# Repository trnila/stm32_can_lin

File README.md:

# STM32 Triple CAN/LIN USB bridge
STM32G4xx firmware written in Rust using the Embassy framework that bridges CAN-FD buses to Linux via USB using the `gs_usb` driver and socketCAN interface.

- 3x CAN-FD channels
    - configurable 120Ω termination resistor

## Build & flash & run
Install Rust via [rustup.rs](https://rustup.rs/).

Set `nSWBOOT0` to 0 using STM32CubeProgrammer for the first time, then connect the debugger and flash the device:
```sh
$ cargo run --release
```

Three socketCAN interfaces will appear, for example as `can0`, `can1`, and `can2`.
You can configure them using `ip` command:
```sh
$ sudo ip link set can0 type can bitrate 500000
$ sudo ip link set can0 up
```

After that, you can start sending and receiving CAN frames:
```sh
$ candump can0
$ cansend can0 123#abcd
```

## Configuration
All configurations must be done while the interface is in the `down` state.
```sh
$ sudo ip link set can0 down
```
After the configuration, bring the interface `up`.

### CAN-FD mode and data bitrate
Set CAN to 500 Kbps and CAN-FD to 1 Mbps:
```sh
$ sudo ip link set can0 type can bitrate 500000 fd on dbitrate 1000000
```

### 120Ω termination resistor
Termination resistor can be enabled in configuration mode via:
```sh
$ sudo ip link set can0 down
$ sudo ip link set can0 type can bitrate 500000 termination 120
$ sudo ip link set can0 up
```

### Persistent interface names
Configure udev rules (`/etc/udev/rules.d/91-scan.rules`) for persistent interface names:
```
SUBSYSTEM=="net", ENV{ID_SERIAL}=="trnila_STM32_CAN_LIN_1", ATTR{dev_id}=="0x0", NAME="scan0"
SUBSYSTEM=="net", ENV{ID_SERIAL}=="trnila_STM32_CAN_LIN_1", ATTR{dev_id}=="0x1", NAME="scan1"
SUBSYSTEM=="net", ENV{ID_SERIAL}=="trnila_STM32_CAN_LIN_1", ATTR{dev_id}=="0x2", NAME="scan2"
```
and then reload `sudo udevadm control --reload-rules` and re-plug the device.

## Test
Install following dependencies:
- uv
- [can-utils](https://github.com/linux-can/can-utils)

Next, connect the DUT's `can0` interface to the tester's `can1_0` interface, and so on. Then run:
```sh
$ CAN_IFACES=0:can0:can1_0,1:can1:can1_1,2:can2:can0_0 ./hw_test.py
```

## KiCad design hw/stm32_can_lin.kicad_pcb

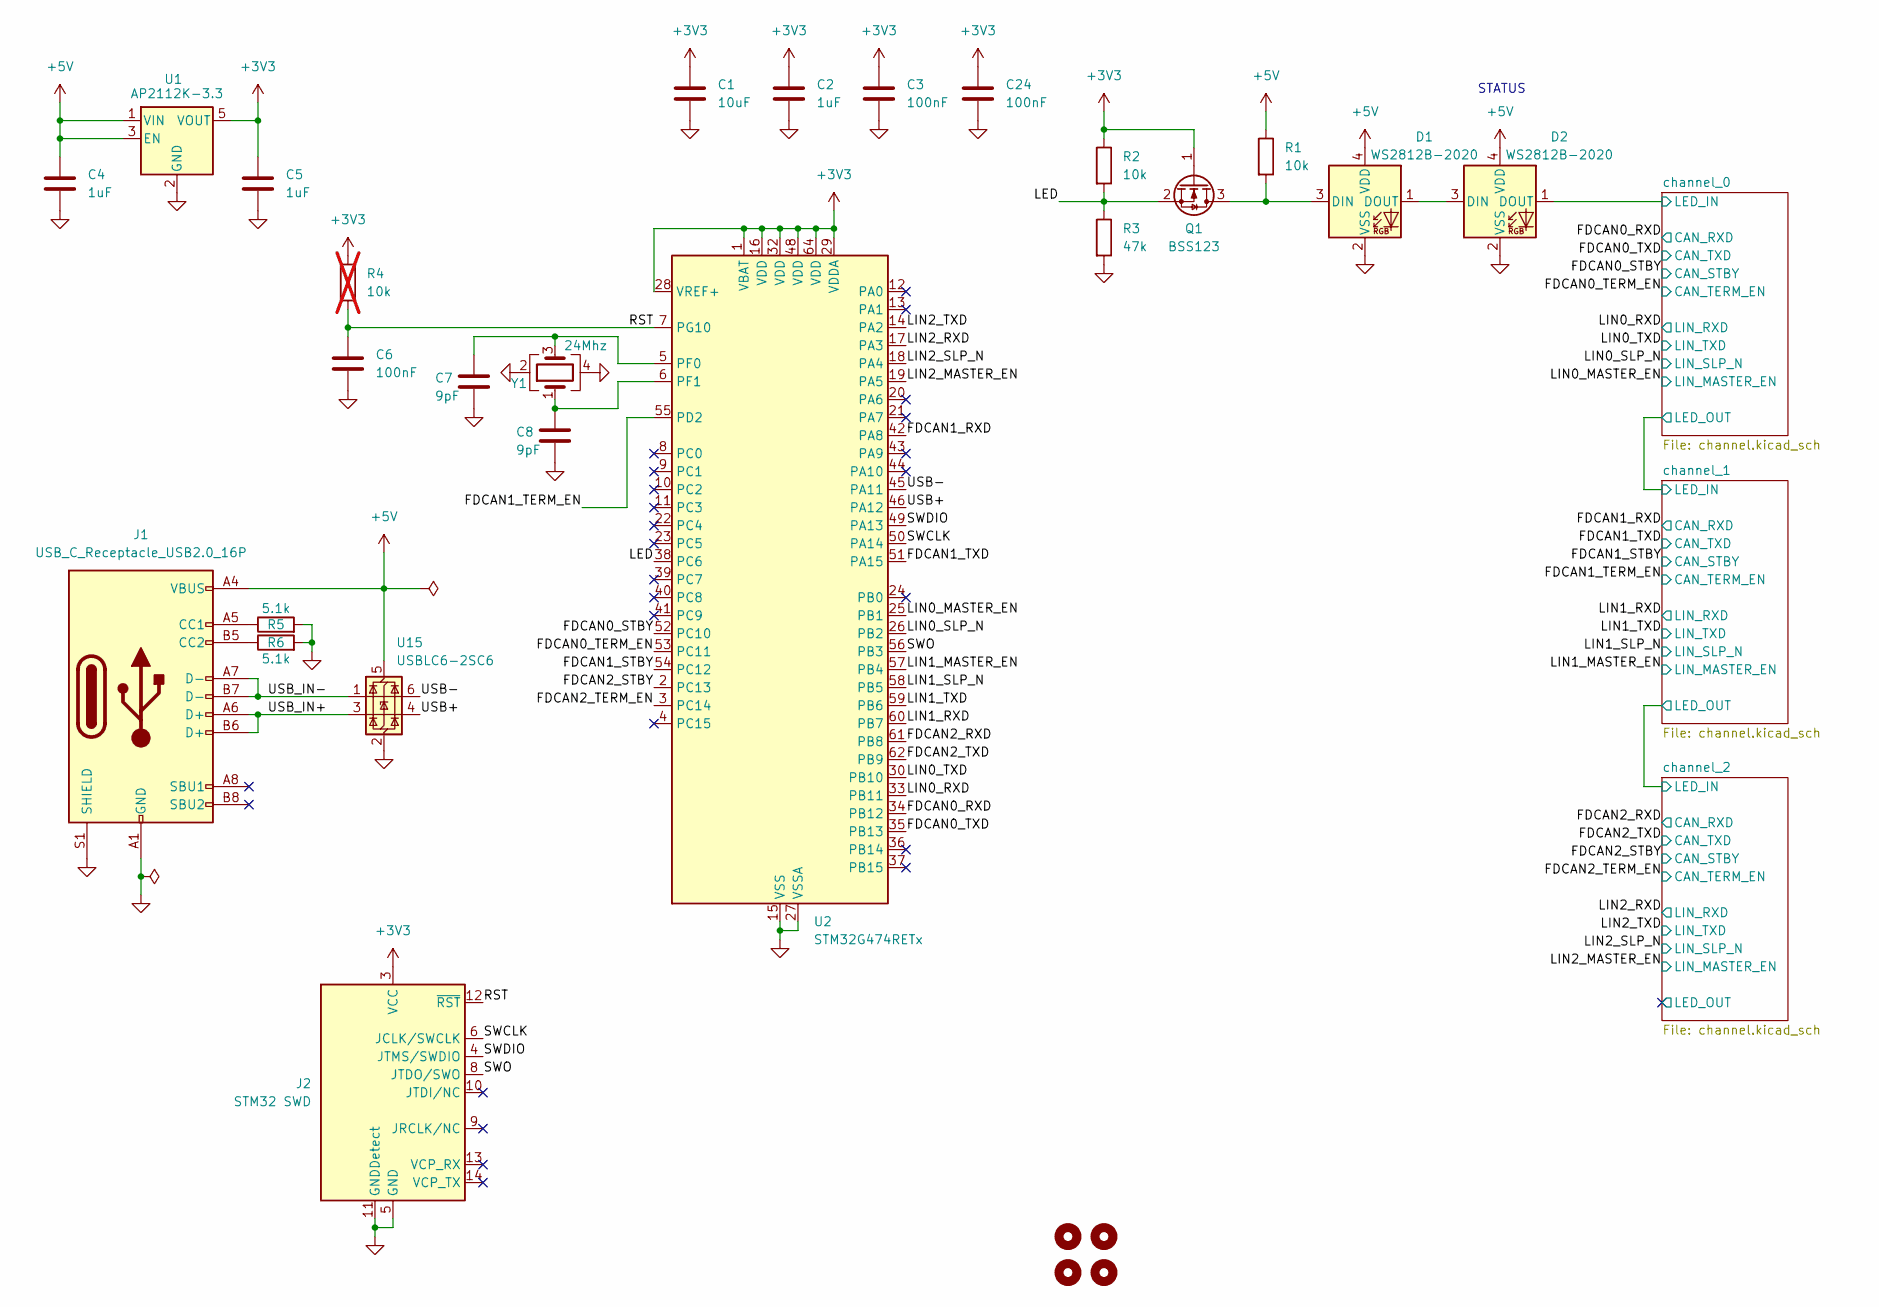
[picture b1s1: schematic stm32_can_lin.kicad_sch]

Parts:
C1: 10uF; C_0805_2012Metric_Pad1.18x1.45mm_HandSolder
C2, C4, C5: 1uF; C_0805_2012Metric_Pad1.18x1.45mm_HandSolder
C3, C6, C24: 100nF; C_0805_2012Metric_Pad1.18x1.45mm_HandSolder
C7, C8: 9pF; C_0805_2012Metric_Pad1.18x1.45mm_HandSolder
D1, D2: WS2812B-2020; LED_WS2812B-2020_PLCC4_2.0x2.0mm
H1, H2, H3, H4: MountingHole; MountingHole_3.2mm_M3
J1: USB_C_Receptacle_USB2.0_16P; USB_C_Receptacle_GCT_USB4105-xx-A_16P_TopMnt_Horizontal
J2: STM32 SWD; PinHeader_2x07_P1.27mm_Vertical_SMD
Q1: BSS123; SOT-23
R1, R2: 10k; R_0805_2012Metric_Pad1.20x1.40mm_HandSolder
R3: 47k; R_0805_2012Metric_Pad1.20x1.40mm_HandSolder
R4: 10k; R_0805_2012Metric_Pad1.20x1.40mm_HandSolder; not fitted
R5, R6: 5.1k; R_0805_2012Metric_Pad1.20x1.40mm_HandSolder
U1: AP2112K-3.3; SOT-23-5
U2: STM32G474RETx; LQFP-64_10x10mm_P0.5mm
U15: USBLC6-2SC6; SOT-23-6
Y1: 24Mhz; Crystal_SMD_3225-4Pin_3.2x2.5mm_HandSoldering

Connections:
+3V3: C1.1, C2.1, C3.1, C5.1, C24.1, J2.3 (VCC), Q1.1 (G), R2.1, R4.1, U1.5 (VOUT), U2.1 (VBAT), U2.16 (VDD), U2.28 (VREF+), U2.29 (VDDA), U2.32 (VDD), U2.48 (VDD), U2.64 (VDD); also elsewhere on the board
+5V: C4.1, D1.4 (VDD), D2.4 (VDD), J1.A4 (VBUS), J1.A9 (VBUS), J1.B4 (VBUS), J1.B9 (VBUS), R1.1, U1.1 (VIN), U1.3 (EN), U15.5 (VBUS); also elsewhere on the board
/FDCAN0_RXD: U2.34 (PB12); also elsewhere on the board
/FDCAN0_STBY: U2.52 (PC10); also elsewhere on the board
/FDCAN0_TERM_EN: U2.53 (PC11); also elsewhere on the board
/FDCAN0_TXD: U2.35 (PB13); also elsewhere on the board
/FDCAN1_RXD: U2.42 (PA8); also elsewhere on the board
/FDCAN1_STBY: U2.54 (PC12); also elsewhere on the board
/FDCAN1_TERM_EN: U2.55 (PD2); also elsewhere on the board
/FDCAN1_TXD: U2.51 (PA15); also elsewhere on the board
/FDCAN2_RXD: U2.61 (PB8); also elsewhere on the board
/FDCAN2_STBY: U2.2 (PC13); also elsewhere on the board
/FDCAN2_TERM_EN: U2.3 (PC14); also elsewhere on the board
/FDCAN2_TXD: U2.62 (PB9); also elsewhere on the board
/LED: Q1.2 (S), R2.2, R3.1, U2.38 (PC6)
/LIN0_MASTER_EN: U2.25 (PB1); also elsewhere on the board
/LIN0_RXD: U2.33 (PB11); also elsewhere on the board
/LIN0_SLP_N: U2.26 (PB2); also elsewhere on the board
/LIN0_TXD: U2.30 (PB10); also elsewhere on the board
/LIN1_MASTER_EN: U2.57 (PB4); also elsewhere on the board
/LIN1_RXD: U2.60 (PB7); also elsewhere on the board
/LIN1_SLP_N: U2.58 (PB5); also elsewhere on the board
/LIN1_TXD: U2.59 (PB6); also elsewhere on the board
/LIN2_MASTER_EN: U2.19 (PA5); also elsewhere on the board
/LIN2_RXD: U2.17 (PA3); also elsewhere on the board
/LIN2_SLP_N: U2.18 (PA4); also elsewhere on the board
/LIN2_TXD: U2.14 (PA2); also elsewhere on the board
/RST: C6.1, J2.12 (~RST), R4.2, U2.7 (PG10)
/SWCLK: J2.6 (JCLK/SWCLK), U2.50 (PA14)
/SWDIO: J2.4 (JTMS/SWDIO), U2.49 (PA13)
/SWO: J2.8 (JTDO/SWO), U2.56 (PB3)
/USB+: U2.46 (PA12), U15.4 (I/O2)
/USB-: U2.45 (PA11), U15.6 (I/O1)
/USB_IN+: J1.A6 (D+), J1.B6 (D+), U15.3 (I/O2)
/USB_IN-: J1.A7 (D-), J1.B7 (D-), U15.1 (I/O1)
/channel_0/LED_IN: D2.1 (DOUT); also elsewhere on the board
GND: C1.2, C2.2, C3.2, C4.2, C5.2, C6.2, C7.1, C8.1, C24.2, D1.2 (VSS), D2.2 (VSS), J1.A1 (GND), J1.A12 (GND), J1.B1 (GND), J1.B12 (GND), J1.S1 (SHIELD), J2.5 (GND), J2.7 (GND), J2.11 (GNDDetect), R3.2, R5.2, R6.2, U1.2 (GND), U2.15 (VSS), U2.27 (VSSA), U2.31 (VSS), U2.47 (VSS), U2.63 (VSS), U15.2 (GND), Y1.2, Y1.4; also elsewhere on the board
unnamed: D1.3 (DIN), Q1.3 (D), R1.2
unnamed: D1.1 (DOUT), D2.3 (DIN)
unnamed: J1.A5 (CC1), R5.1
unnamed: J1.B5 (CC2), R6.1
unnamed: C7.2, U2.5 (PF0), Y1.3
unnamed: C8.2, U2.6 (PF1), Y1.1

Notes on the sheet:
STATUS

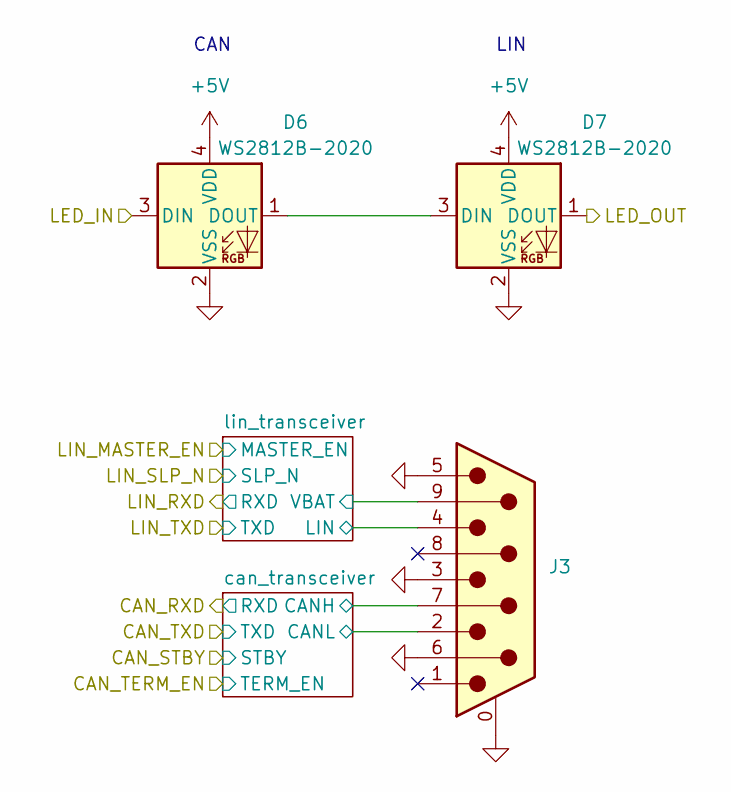
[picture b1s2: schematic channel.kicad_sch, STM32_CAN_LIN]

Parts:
D6, D7: WS2812B-2020; LED_WS2812B-2020_PLCC4_2.0x2.0mm
J3: DE9_Pins_MountingHoles; DSUB-9_Pins_Horizontal_P2.77x2.84mm_EdgePinOffset7.70mm_Hou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

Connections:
+5V: D6.4 (VDD), D7.4 (VDD); also elsewhere on the board
/channel_0/LED_IN: D6.3 (DIN); also elsewhere on the board
/channel_0/LED_OUT: D7.1 (DOUT); also elsewhere on the board
/channel_0/can_transceiver/CANH: J3.7; also elsewhere on the board
/channel_0/can_transceiver/CANL: J3.2; also elsewhere on the board
/channel_0/lin_transceiver/LIN: J3.4; also elsewhere on the board
/channel_0/lin_transceiver/VBAT: J3.9; also elsewhere on the board
GND: D6.2 (VSS), D7.2 (VSS), J3.0 (PAD), J3.3, J3.5, J3.6; also elsewhere on the board
unnamed: D6.1 (DOUT), D7.3 (DIN)

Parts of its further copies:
D8, D9, D13, D14: WS2812B-2020; LED_WS2812B-2020_PLCC4_2.0x2.0mm
J4, J5: DE9_Pins_MountingHoles; DSUB-9_Pins_Horizontal_P2.77x2.84mm_EdgePinOffset7.70mm_Hou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

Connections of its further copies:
+5V: D8.4 (VDD), D9.4 (VDD), D13.4 (VDD), D14.4 (VDD); also elsewhere on the board
/channel_0/LED_OUT: D8.3 (DIN); also elsewhere on the board
/channel_1/LED_OUT: D9.1 (DOUT), D13.3 (DIN)
/channel_1/can_transceiver/CANH: J4.7; also elsewhere on the board
/channel_1/can_transceiver/CANL: J4.2; also elsewhere on the board
/channel_1/lin_transceiver/LIN: J4.4; also elsewhere on the board
/channel_1/lin_transceiver/VBAT: J4.9; also elsewhere on the board
/channel_2/LED_OUT: D14.1 (DOUT)
/channel_2/can_transceiver/CANH: J5.7; also elsewhere on the board
/channel_2/can_transceiver/CANL: J5.2; also elsewhere on the board
/channel_2/lin_transceiver/LIN: J5.4; also elsewhere on the board
/channel_2/lin_transceiver/VBAT: J5.9; also elsewhere on the board
GND: D8.2 (VSS), D9.2 (VSS), D13.2 (VSS), D14.2 (VSS), J4.0 (PAD), J4.3, J4.5, J4.6, J5.0 (PAD), J5.3, J5.5, J5.6; also elsewhere on the board
unnamed: D8.1 (DOUT), D9.3 (DIN)
unnamed: D13.1 (DOUT), D14.3 (DIN)

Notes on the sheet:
CAN
LIN

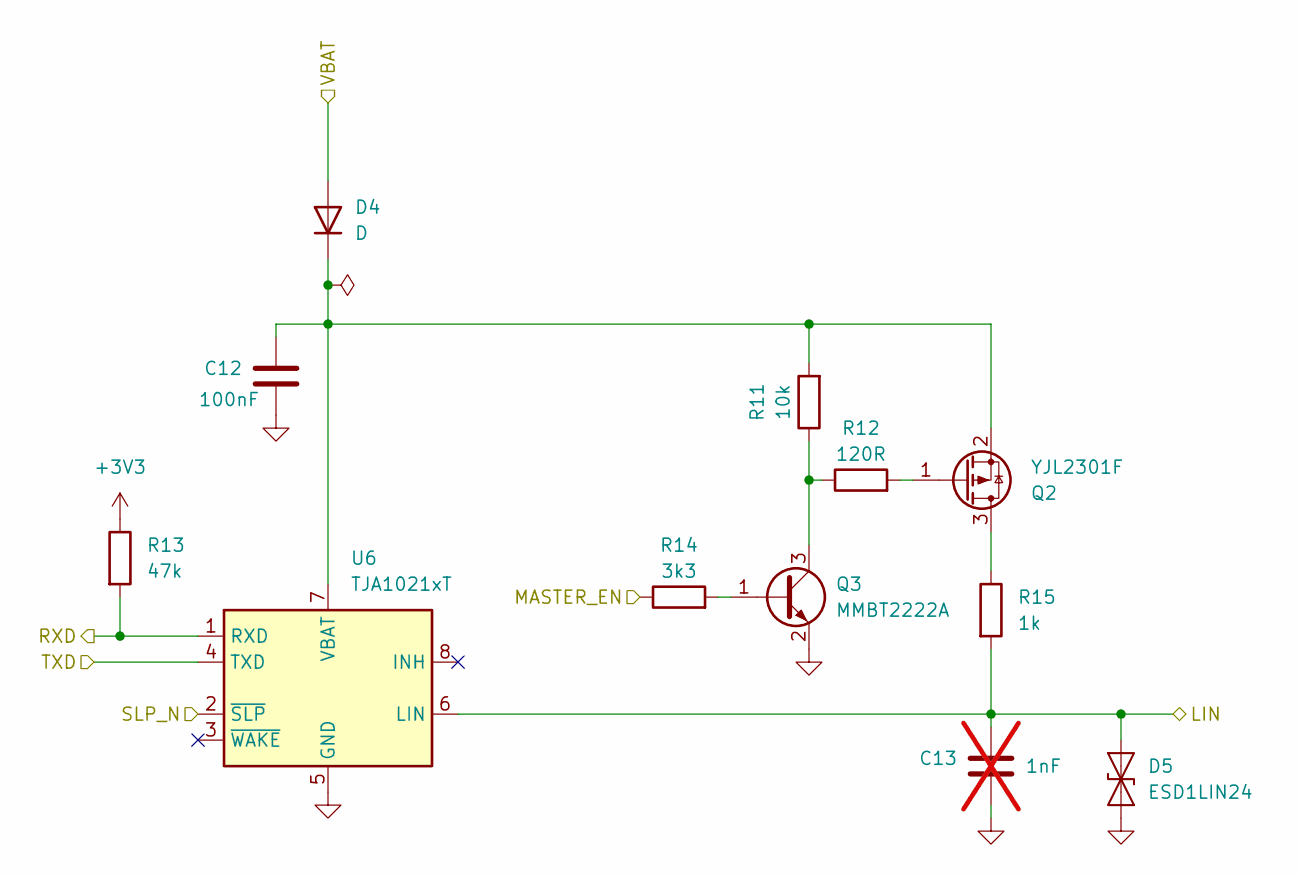
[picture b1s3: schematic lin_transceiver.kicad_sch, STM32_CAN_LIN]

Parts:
C12: 100nF; C_0805_2012Metric_Pad1.18x1.45mm_HandSolder
C13: 1nF; C_0805_2012Metric_Pad1.18x1.45mm_HandSolder; not fitted
D4: D; D_SOD-323_HandSoldering
D5: ESD1LIN24; D_SOD-923
Q2: YJL2301F; SOT-23_Handsoldering
Q3: MMBT2222A; SOT-23_Handsoldering
R11: 10k; R_0805_2012Metric_Pad1.20x1.40mm_HandSolder
R12: 120R; R_0805_2012Metric_Pad1.20x1.40mm_HandSolder
R13: 47k; R_0805_2012Metric_Pad1.20x1.40mm_HandSolder
R14: 3k3; R_0805_2012Metric_Pad1.20x1.40mm_HandSolder
R15: 1k; R_0805_2012Metric_Pad1.20x1.40mm_HandSolder
U6: TJA1021xT; SOIC-8_3.9x4.9mm_P1.27mm

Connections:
+3V3: R13.1; also elsewhere on the board
/LIN0_MASTER_EN: R14.1; also elsewhere on the board
/LIN0_RXD: R13.2, U6.1 (RXD); also elsewhere on the board
/LIN0_SLP_N: U6.2 (~SLP); also elsewhere on the board
/LIN0_TXD: U6.4 (TXD); also elsewhere on the board
/channel_0/lin_transceiver/LIN: C13.1, D5.2 (A2), R15.2, U6.6 (LIN); also elsewhere on the board
/channel_0/lin_transceiver/VBAT: D4.2 (A); also elsewhere on the board
GND: C12.2, C13.2, D5.1 (A1), Q3.2 (E), U6.5 (GND); also elsewhere on the board
unnamed: C12.1, D4.1 (K), Q2.2 (S), R11.2, U6.7 (VBAT)
unnamed: Q2.3 (D), R15.1
unnamed: Q2.1 (G), R12.2
unnamed: Q3.1 (B), R14.2
unnamed: Q3.3 (C), R11.1, R12.1

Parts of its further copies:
C17, C22: 100nF; C_0805_2012Metric_Pad1.18x1.45mm_HandSolder
C18, C23: 1nF; C_0805_2012Metric_Pad1.18x1.45mm_HandSolder; not fitted
D11, D16: D; D_SOD-323_HandSoldering
D12, D17: ESD1LIN24; D_SOD-923
Q4, Q6: YJL2301F; SOT-23_Handsoldering
Q5, Q7: MMBT2222A; SOT-23_Handsoldering
R20, R29: 10k; R_0805_2012Metric_Pad1.20x1.40mm_HandSolder
R21, R30: 120R; R_0805_2012Metric_Pad1.20x1.40mm_HandSolder
R22, R31: 47k; R_0805_2012Metric_Pad1.20x1.40mm_HandSolder
R23, R32: 3k3; R_0805_2012Metric_Pad1.20x1.40mm_HandSolder
R24, R33: 1k; R_0805_2012Metric_Pad1.20x1.40mm_HandSolder
U10, U14: TJA1021xT; SOIC-8_3.9x4.9mm_P1.27mm

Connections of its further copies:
+3V3: R22.1, R31.1; also elsewhere on the board
/LIN1_MASTER_EN: R23.1; also elsewhere on the board
/LIN1_RXD: R22.2, U10.1 (RXD); also elsewhere on the board
/LIN1_SLP_N: U10.2 (~SLP); also elsewhere on the board
/LIN1_TXD: U10.4 (TXD); also elsewhere on the board
/LIN2_MASTER_EN: R32.1; also elsewhere on the board
/LIN2_RXD: R31.2, U14.1 (RXD); also elsewhere on the board
/LIN2_SLP_N: U14.2 (~SLP); also elsewhere on the board
/LIN2_TXD: U14.4 (TXD); also elsewhere on the board
/channel_1/lin_transceiver/LIN: C18.1, D12.2 (A2), R24.2, U10.6 (LIN); also elsewhere on the board
/channel_1/lin_transceiver/VBAT: D11.2 (A); also elsewhere on the board
/channel_2/lin_transceiver/LIN: C23.1, D17.2 (A2), R33.2, U14.6 (LIN); also elsewhere on the board
/channel_2/lin_transceiver/VBAT: D16.2 (A); also elsewhere on the board
GND: C17.2, C18.2, C22.2, C23.2, D12.1 (A1), D17.1 (A1), Q5.2 (E), Q7.2 (E), U10.5 (GND), U14.5 (GND); also elsewhere on the board
unnamed: C17.1, D11.1 (K), Q4.2 (S), R20.2, U10.7 (VBAT)
unnamed: C22.1, D16.1 (K), Q6.2 (S), R29.2, U14.7 (VBAT)
unnamed: Q4.3 (D), R24.1
unnamed: Q4.1 (G), R21.2
unnamed: Q5.1 (B), R23.2
unnamed: Q5.3 (C), R20.1, R21.1
unnamed: Q6.3 (D), R33.1
unnamed: Q6.1 (G), R30.2
unnamed: Q7.1 (B), R32.2
unnamed: Q7.3 (C), R29.1, R30.1

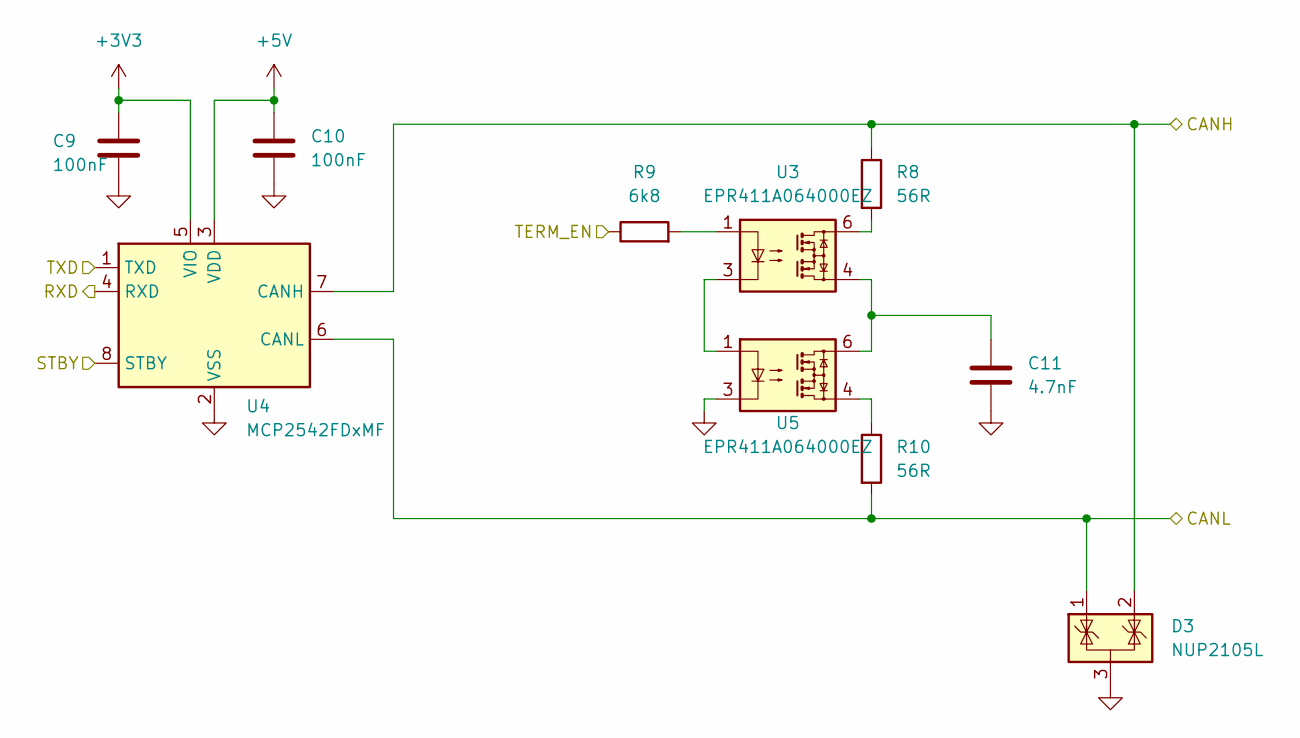
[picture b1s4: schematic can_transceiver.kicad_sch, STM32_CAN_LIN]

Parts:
C9, C10: 100nF; C_0805_2012Metric_Pad1.18x1.45mm_HandSolder
C11: 4.7nF; C_0805_2012Metric_Pad1.18x1.45mm_HandSolder
D3: NUP2105L; SOT-23
R8, R10: 56R; R_0805_2012Metric_Pad1.20x1.40mm_HandSolder
R9: 6k8; R_0805_2012Metric_Pad1.20x1.40mm_HandSolder
U3, U5: EPR411A064000EZ; SOIC-4_4.7_4.4_P2.54
U4: MCP2542FDxMF; SOIC-8_3.9x4.9mm_P1.27mm

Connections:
+3V3: C9.1, U4.5 (VIO); also elsewhere on the board
+5V: C10.1, U4.3 (VDD); also elsewhere on the board
/FDCAN0_RXD: U4.4 (RXD); also elsewhere on the board
/FDCAN0_STBY: U4.8 (STBY); also elsewhere on the board
/FDCAN0_TERM_EN: R9.1; also elsewhere on the board
/FDCAN0_TXD: U4.1 (TXD); also elsewhere on the board
/channel_0/can_transceiver/CANH: D3.2 (K), R8.1, U4.7 (CANH); also elsewhere on the board
/channel_0/can_transceiver/CANL: D3.1 (K), R10.2, U4.6 (CANL); also elsewhere on the board
GND: C9.2, C10.2, C11.2, D3.3 (A), U4.2 (VSS), U5.3; also elsewhere on the board
unnamed: C11.1, U3.4, U5.6
unnamed: R8.2, U3.6
unnamed: R9.2, U3.1
unnamed: R10.1, U5.4
unnamed: U3.3, U5.1

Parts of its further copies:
C14, C15, C19, C20: 100nF; C_0805_2012Metric_Pad1.18x1.45mm_HandSolder
C16, C21: 4.7nF; C_0805_2012Metric_Pad1.18x1.45mm_HandSolder
D10, D15: NUP2105L; SOT-23
R17, R19, R26, R28: 56R; R_0805_2012Metric_Pad1.20x1.40mm_HandSolder
R18, R27: 6k8; R_0805_2012Metric_Pad1.20x1.40mm_HandSolder
U7, U9, U11, U13: EPR411A064000EZ; SOIC-4_4.7_4.4_P2.54
U8, U12: MCP2542FDxMF; SOIC-8_3.9x4.9mm_P1.27mm

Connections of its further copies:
+3V3: C14.1, C19.1, U8.5 (VIO), U12.5 (VIO); also elsewhere on the board
+5V: C15.1, C20.1, U8.3 (VDD), U12.3 (VDD); also elsewhere on the board
/FDCAN1_RXD: U8.4 (RXD); also elsewhere on the board
/FDCAN1_STBY: U8.8 (STBY); also elsewhere on the board
/FDCAN1_TERM_EN: R18.1; also elsewhere on the board
/FDCAN1_TXD: U8.1 (TXD); also elsewhere on the board
/FDCAN2_RXD: U12.4 (RXD); also elsewhere on the board
/FDCAN2_STBY: U12.8 (STBY); also elsewhere on the board
/FDCAN2_TERM_EN: R27.1; also elsewhere on the board
/FDCAN2_TXD: U12.1 (TXD); also elsewhere on the board
/channel_1/can_transceiver/CANH: D10.2 (K), R17.1, U8.7 (CANH); also elsewhere on the board
/channel_1/can_transceiver/CANL: D10.1 (K), R19.2, U8.6 (CANL); also elsewhere on the board
/channel_2/can_transceiver/CANH: D15.2 (K), R26.1, U12.7 (CANH); also elsewhere on the board
/channel_2/can_transceiver/CANL: D15.1 (K), R28.2, U12.6 (CANL); also elsewhere on the board
GND: C14.2, C15.2, C16.2, C19.2, C20.2, C21.2, D10.3 (A), D15.3 (A), U8.2 (VSS), U9.3, U12.2 (VSS), U13.3; also elsewhere on the board
unnamed: C16.1, U7.4, U9.6
unnamed: C21.1, U11.4, U13.6
unnamed: R17.2, U7.6
unnamed: R18.2, U7.1
unnamed: R19.1, U9.4
unnamed: R26.2, U11.6
unnamed: R27.2, U11.1
unnamed: R28.1, U13.4
unnamed: U7.3, U9.1
unnamed: U11.3, U13.1

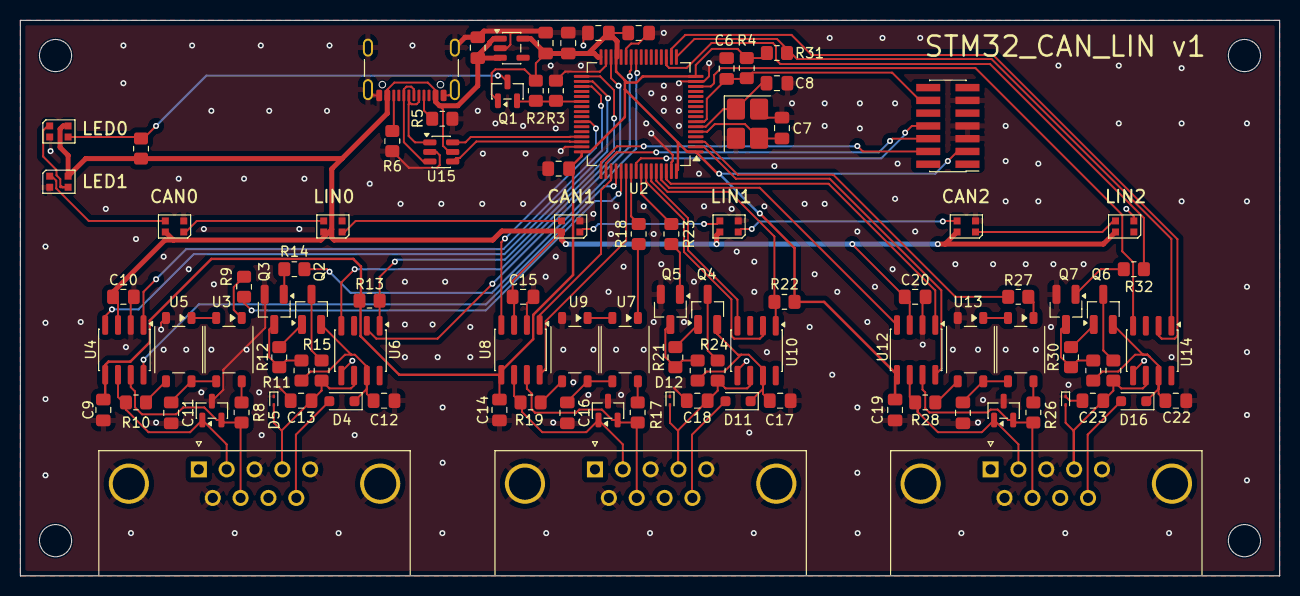
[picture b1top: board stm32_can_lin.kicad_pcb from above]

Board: 2 copper layers, 125.2 x 55.2 mm, 103 parts (0 on the bottom side), 90 nets.

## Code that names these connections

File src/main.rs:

#![no_std]
#![no_main]

use crate::can::can_usb_bridge;
use crate::gs_usb::CHANNEL_QUEUE_SIZE;
use crate::gs_usb::USB_QUEUE_SIZE;
use crate::gs_usb::UsbCommand;
use crate::gs_usb::UsbCommandQueues;
use crate::gs_usb::UsbResponse;
use crate::gs_usb::usb_init;
use embassy_executor::Spawner;
use embassy_stm32::bind_interrupts;
use embassy_stm32::can::CanConfigurator;
use embassy_stm32::gpio::Level;
use embassy_stm32::gpio::Output;
use embassy_stm32::gpio::Speed;
use embassy_stm32::peripherals;
use embassy_stm32::rcc;
use embassy_stm32::time::mhz;
use embassy_stm32::usb::Driver;
use embassy_sync::blocking_mutex::raw::ThreadModeRawMutex;
use embassy_sync::channel::Channel;
use {defmt_rtt as _, panic_probe as _};

mod can;
mod gs_usb;

static USB_CMDS_CH0: Channel<ThreadModeRawMutex, UsbCommand, CHANNEL_QUEUE_SIZE> = Channel::new();
static USB_CMDS_CH1: Channel<ThreadModeRawMutex, UsbCommand, CHANNEL_QUEUE_SIZE> = Channel::new();
static USB_CMDS_CH2: Channel<ThreadModeRawMutex, UsbCommand, CHANNEL_QUEUE_SIZE> = Channel::new();
static USB_RESPS: Channel<ThreadModeRawMutex, UsbResponse, USB_QUEUE_SIZE> = Channel::new();

bind_interrupts!(struct Irqs {
    USB_LP => embassy_stm32::usb::InterruptHandler<peripherals::USB>;
    FDCAN1_IT0 => embassy_stm32::can::IT0InterruptHandler<peripherals::FDCAN1>;
    FDCAN1_IT1 => embassy_stm32::can::IT1InterruptHandler<peripherals::FDCAN1>;
    FDCAN2_IT0 => embassy_stm32::can::IT0InterruptHandler<peripherals::FDCAN2>;
    FDCAN2_IT1 => embassy_stm32::can::IT1InterruptHandler<peripherals::FDCAN2>;
    FDCAN3_IT0 => embassy_stm32::can::IT0InterruptHandler<peripherals::FDCAN3>;
    FDCAN3_IT1 => embassy_stm32::can::IT1InterruptHandler<peripherals::FDCAN3>;
});

#[embassy_executor::main]
async fn main(spawner: Spawner) {
    let p = embassy_stm32::init({
        let mut config = embassy_stm32::Config::default();
        config.rcc.hsi = false;
        config.rcc.hse = Some(rcc::Hse {
            freq: mhz(24),
            mode: rcc::HseMode::Oscillator,
        });
        config.rcc.sys = rcc::Sysclk::Pll1R;
        config.rcc.pll = Some(rcc::Pll {
            source: rcc::PllSource::Hse,
            prediv: rcc::PllPreDiv::Div6,
            mul: rcc::PllMul::Mul85,
            divr: Some(rcc::PllRDiv::Div2),
            divq: Some(rcc::PllQDiv::Div2),
            divp: Some(rcc::PllPDiv::Div2),
        });
        config.rcc.ahb_pre = rcc::AHBPrescaler::Div1;
        config.rcc.apb1_pre = rcc::APBPrescaler::Div2;
        config.rcc.mux.fdcansel = rcc::mux::Fdcansel::Hse;
        config
    });

    // FDCAN0
    spawner.spawn(
        can_usb_bridge(
            0,
            CanConfigurator::new(p.FDCAN2, p.PB12, p.PB13, Irqs),
            Output::new(p.PC10, Level::Low, Speed::Low),
            Output::new(p.PC11, Level::Low, Speed::Low),
            USB_CMDS_CH0.receiver(),
            USB_RESPS.sender(),
        )
        .unwrap(),
    );

    // FDCAN1
    spawner.spawn(
        can_usb_bridge(
            1,
            CanConfigurator::new(p.FDCAN3, p.PA8, p.PA15, Irqs),
            Output::new(p.PC12, Level::Low, Speed::Low),
            Output::new(p.PD2, Level::Low, Speed::Low),
            USB_CMDS_CH1.receiver(),
            USB_RESPS.sender(),
        )
        .unwrap(),
    );

    // FDCAN2
    spawner.spawn(
        can_usb_bridge(
            2,
            CanConfigurator::new(p.FDCAN1, p.PB8, p.PB9, Irqs),
            Output::new(p.PC13, Level::Low, Speed::Low),
            Output::new(p.PC14, Level::Low, Speed::Low),
            USB_CMDS_CH2.receiver(),
            USB_RESPS.sender(),
        )
        .unwrap(),
    );

    let usb = Driver::new(p.USB, Irqs, p.PA12, p.PA11);
    spawner.spawn(
        usb_init(
            usb,
            USB_RESPS.receiver(),
            UsbCommandQueues {
                channel: [
                    USB_CMDS_CH0.sender(),
                    USB_CMDS_CH1.sender(),
                    USB_CMDS_CH2.sender(),
                ],
            },
        )
        .unwrap(),
    );
}

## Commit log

2025-12-07 HW initial commit v1
2026-01-02 ci: added lint and build workflow
    - run pre-commit mainly with clippy/rustfmt
    - build release firmware
2026-01-02 hw_test.py: use canfdtest from can-utils to test full duplex communication
2026-01-02 minimalistic gs_usb CAN-only firmware
2026-01-03 read/write full USB transfer split across multiple packets
2026-01-03 hw_test.py: canfdtest with extended frames and different payload sizes
2026-01-03 fixed UsbResponseTx queue size to USB_QUEUE_SIZE
2026-01-08 hw: added board photo
2026-01-24 bigger queues
2026-01-24 add support to CAN-FD
2026-01-24 hw_test.py: extract parsing channel interfaces into the function
2026-01-24 hw_test.py: check exit codes of ip command
2026-01-24 configurable CAN termination resistor
2026-03-14 README: configure persistent interface names
2026-06-16 upgrade dependencies
